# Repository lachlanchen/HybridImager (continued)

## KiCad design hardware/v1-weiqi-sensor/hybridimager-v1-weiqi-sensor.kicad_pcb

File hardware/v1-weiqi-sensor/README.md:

# HybridImager V1 Weiqi Sparse Sensor Board

This is the first board-level HybridImager sensor draft. It deliberately uses a
**sparse multi-site single-pixel detector array** instead of one central bucket
only. The geometry follows a Weiqi-like 7x7 conceptual grid with 21 populated
detector sites.

## Immediate Scope

- Validate detector spacing and sparse reconstruction geometry.
- Provide per-site signal pads for external TIA/comparator experiments.
- Reserve board area for three TIA banks, one timestamp MCU/FPGA, sync SMA
  connectors, power/sync header, and a 2x20 expansion header.
- Keep V1 buildable and inspectable before committing to dense custom sensor
  electronics or ASIC work.

## Files

- `hybridimager-v1-weiqi-sensor.kicad_pcb`: generated KiCad board.
- `hybridimager-v1-weiqi-sensor.kicad_pro`: KiCad project file.
- `hybridimager-v1-weiqi-sensor.kicad_sch`: board-first schematic stub.
- `hybridimager-v1-source-dataset.json`: source assumptions and design dataset.
- `hybridimager-v1-bom.csv`: draft BOM.
- `artifacts/hybridimager-v1-full-view-render.png`: generated full-view 3D concept render.
- `artifacts/hybridimager-v1-kicad-render-full.png`: KiCad-native zoomed-out render.
- `artifacts/hybridimager-v1-kicad-render-close.png`: KiCad-native closer render.
- `artifacts/hybridimager-v1-weiqi-sensor.step`: STEP export.
- `gerber/`: Gerber and drill outputs.

## Reproduce

```bash
python3 scripts/generate_v1_weiqi_sensor_board.py
kicad-cli pcb upgrade hardware/v1-weiqi-sensor/hybridimager-v1-weiqi-sensor.kicad_pcb
kicad-cli pcb drc --format json --severity-all -o hardware/v1-weiqi-sensor/artifacts/drc.json hardware/v1-weiqi-sensor/hybridimager-v1-weiqi-sensor.kicad_pcb
kicad-cli pcb export step --force --include-pads --include-tracks --include-silkscreen --include-soldermask -o hardware/v1-weiqi-sensor/artifacts/hybridimager-v1-weiqi-sensor.step hardware/v1-weiqi-sensor/hybridimager-v1-weiqi-sensor.kicad_pcb
kicad-cli pcb export gerbers --layers F.Cu,B.Cu,F.SilkS,B.SilkS,F.Mask,B.Mask,Edge.Cuts,F.Fab,B.Fab --precision 6 --check-zones -o hardware/v1-weiqi-sensor/gerber hardware/v1-weiqi-sensor/hybridimager-v1-weiqi-sensor.kicad_pcb
kicad-cli pcb export drill --generate-map --map-format svg --generate-report --report-path hardware/v1-weiqi-sensor/artifacts/drill-report.txt -o hardware/v1-weiqi-sensor/gerber hardware/v1-weiqi-sensor/hybridimager-v1-weiqi-sensor.kicad_pcb
xvfb-run -a kicad-cli pcb render --output hardware/v1-weiqi-sensor/artifacts/hybridimager-v1-kicad-render-full.png --width 1800 --height 1200 --background opaque --quality high --floor --perspective --rotate 315,0,35 --zoom 1.0 hardware/v1-weiqi-sensor/hybridimager-v1-weiqi-sensor.kicad_pcb
```

## Engineering Status

Current generated validation: KiCad DRC reports 0 violations and 0 unconnected
items after running the commands above.

This is still an engineering draft. It is useful for visual review, mechanical
planning, sparse-detector geometry, and next-step analog partitioning. It still
needs a detailed schematic, selected photodiode parts, TIA gain/noise analysis,
layout review, and fabrication review before ordering boards.

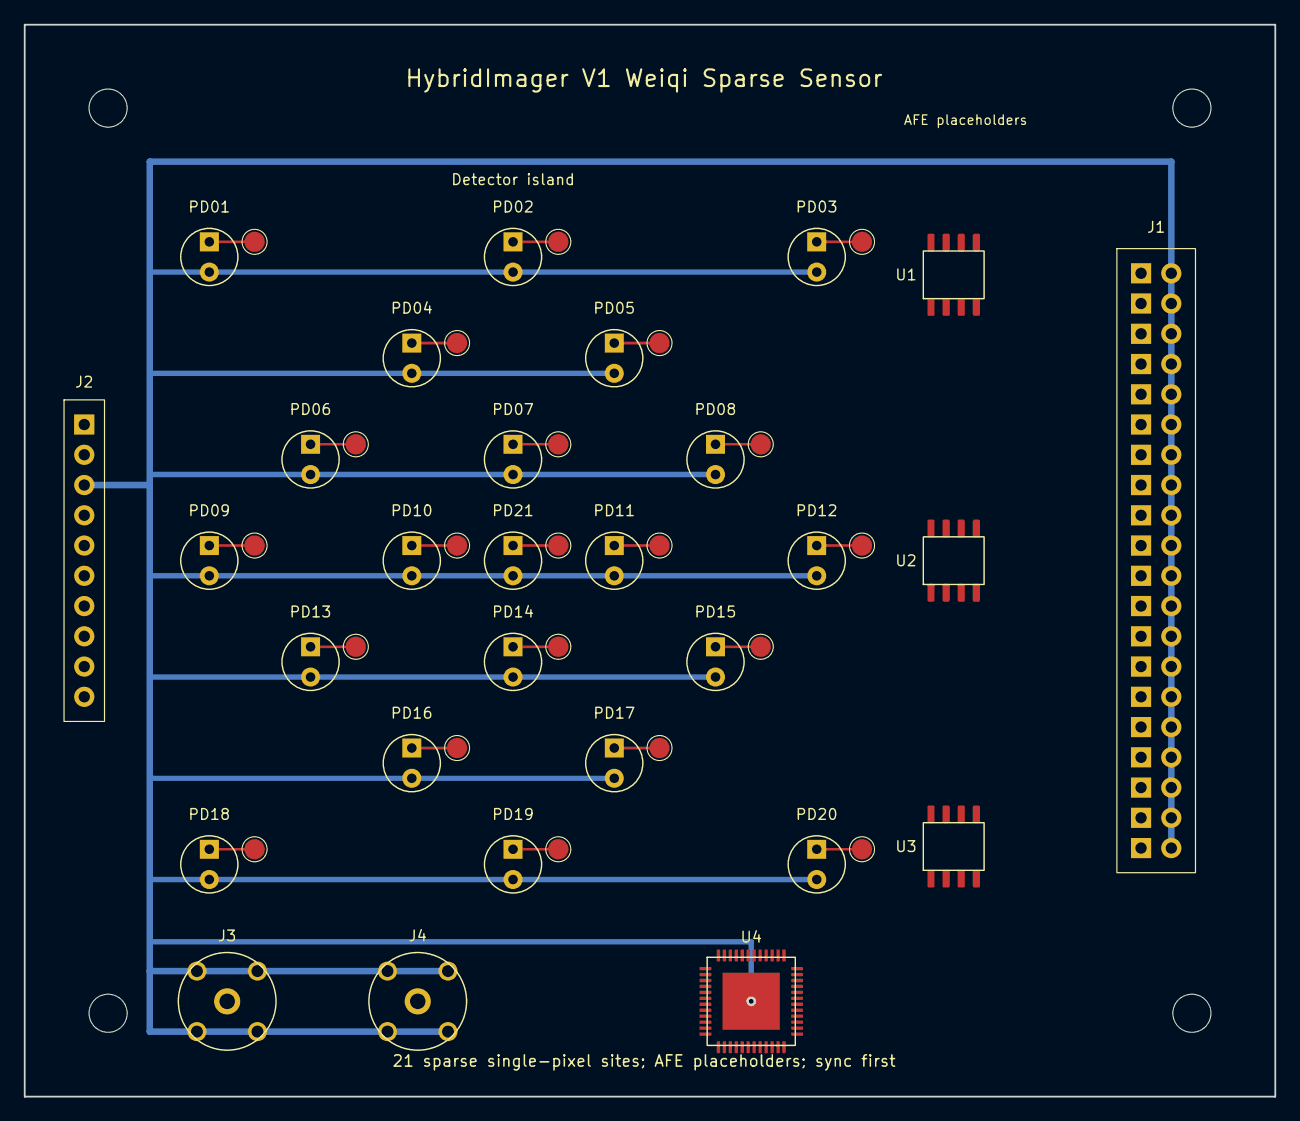
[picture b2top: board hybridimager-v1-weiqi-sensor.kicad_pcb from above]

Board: 2 copper layers, 105.0 x 90.0 mm, 54 parts (0 on the bottom side), 22 nets.

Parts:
H1, H2, H3, H4: M3; MountingHole_3.2mm_M3
J1: AFE_EXPANSION_2x20; PinHeader_2x20_P2.54mm_Vertical
J2: SYNC_PWR_1x10; PinHeader_1x10_P2.54mm_Vertical
J3: SYNC_IN; SMA_Amphenol_132291_Vertical
J4: SYNC_OUT; SMA_Amphenol_132291_Vertical
PD01, PD02, PD03, PD04, PD05, PD06, PD07, PD08, PD09, PD10, PD11, PD12, PD13, PD14, PD15, PD16, PD17, PD18, PD19, PD20, PD21: SPARSE_PHOTODIODE_D3; Sparse_SP_D3_Photodiode
TP01: SP01; TP_1.7mm_SMD
TP02: SP02; TP_1.7mm_SMD
TP03: SP03; TP_1.7mm_SMD
TP04: SP04; TP_1.7mm_SMD
TP05: SP05; TP_1.7mm_SMD
TP06: SP06; TP_1.7mm_SMD
TP07: SP07; TP_1.7mm_SMD
TP08: SP08; TP_1.7mm_SMD
TP09: SP09; TP_1.7mm_SMD
TP10: SP10; TP_1.7mm_SMD
TP11: SP11; TP_1.7mm_SMD
TP12: SP12; TP_1.7mm_SMD
TP13: SP13; TP_1.7mm_SMD
TP14: SP14; TP_1.7mm_SMD
TP15: SP15; TP_1.7mm_SMD
TP16: SP16; TP_1.7mm_SMD
TP17: SP17; TP_1.7mm_SMD
TP18: SP18; TP_1.7mm_SMD
TP19: SP19; TP_1.7mm_SMD
TP20: SP20; TP_1.7mm_SMD
TP21: SP21; TP_1.7mm_SMD
U1, U2, U3: TIA_PLACEHOLDER; SOIC-8_3.9x4.9mm_P1.27mm
U4: TIMESTAMP_MCU_FPGA_PLACEHOLDER; QFN-48-1EP_7x7mm_P0.5mm_EP5.15x5.15mm

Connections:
GND: J1.2 (GND), J1.4 (GND), J1.6 (GND), J1.8 (GND), J1.10 (GND), J1.12 (GND), J1.14 (GND), J1.16 (GND), J1.18 (GND), J1.20 (GND), J1.22 (GND), J1.24 (GND), J1.26 (GND), J1.28 (GND), J1.30 (GND), J1.32 (GND), J1.34 (GND), J1.36 (GND), J1.38 (GND), J1.40 (GND), J2.3 (GND), J3.2 (GND), J3.3 (GND), J3.4 (GND), J3.5 (GND), J4.2 (GND), J4.3 (GND), J4.4 (GND), J4.5 (GND), PD01.G (GUARD), PD02.G (GUARD), PD03.G (GUARD), PD04.G (GUARD), PD05.G (GUARD), PD06.G (GUARD), PD07.G (GUARD), PD08.G (GUARD), PD09.G (GUARD), PD10.G (GUARD), PD11.G (GUARD), PD12.G (GUARD), PD13.G (GUARD), PD14.G (GUARD), PD15.G (GUARD), PD16.G (GUARD), PD17.G (GUARD), PD18.G (GUARD), PD19.G (GUARD), PD20.G (GUARD), PD21.G (GUARD), U4.EP
SP01: PD01.S (SIGNAL), TP01.1 (PROBE)
SP02: PD02.S (SIGNAL), TP02.1 (PROBE)
SP03: PD03.S (SIGNAL), TP03.1 (PROBE)
SP04: PD04.S (SIGNAL), TP04.1 (PROBE)
SP05: PD05.S (SIGNAL), TP05.1 (PROBE)
SP06: PD06.S (SIGNAL), TP06.1 (PROBE)
SP07: PD07.S (SIGNAL), TP07.1 (PROBE)
SP08: PD08.S (SIGNAL), TP08.1 (PROBE)
SP09: PD09.S (SIGNAL), TP09.1 (PROBE)
SP10: PD10.S (SIGNAL), TP10.1 (PROBE)
SP11: PD11.S (SIGNAL), TP11.1 (PROBE)
SP12: PD12.S (SIGNAL), TP12.1 (PROBE)
SP13: PD13.S (SIGNAL), TP13.1 (PROBE)
SP14: PD14.S (SIGNAL), TP14.1 (PROBE)
SP15: PD15.S (SIGNAL), TP15.1 (PROBE)
SP16: PD16.S (SIGNAL), TP16.1 (PROBE)
SP17: PD17.S (SIGNAL), TP17.1 (PROBE)
SP18: PD18.S (SIGNAL), TP18.1 (PROBE)
SP19: PD19.S (SIGNAL), TP19.1 (PROBE)
SP20: PD20.S (SIGNAL), TP20.1 (PROBE)
SP21: PD21.S (SIGNAL), TP21.1 (PROBE)

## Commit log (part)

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2026-06-08 Initialize hybrid camera research package
2026-06-08 Add open camera project survey
2026-06-08 Prepare HybridImager public README
2026-06-08 Add repository citation metadata
2026-06-08 Add V1 Weiqi sparse sensor board
2026-06-08 Add V2 ALS-PT19 aligned matrix board
